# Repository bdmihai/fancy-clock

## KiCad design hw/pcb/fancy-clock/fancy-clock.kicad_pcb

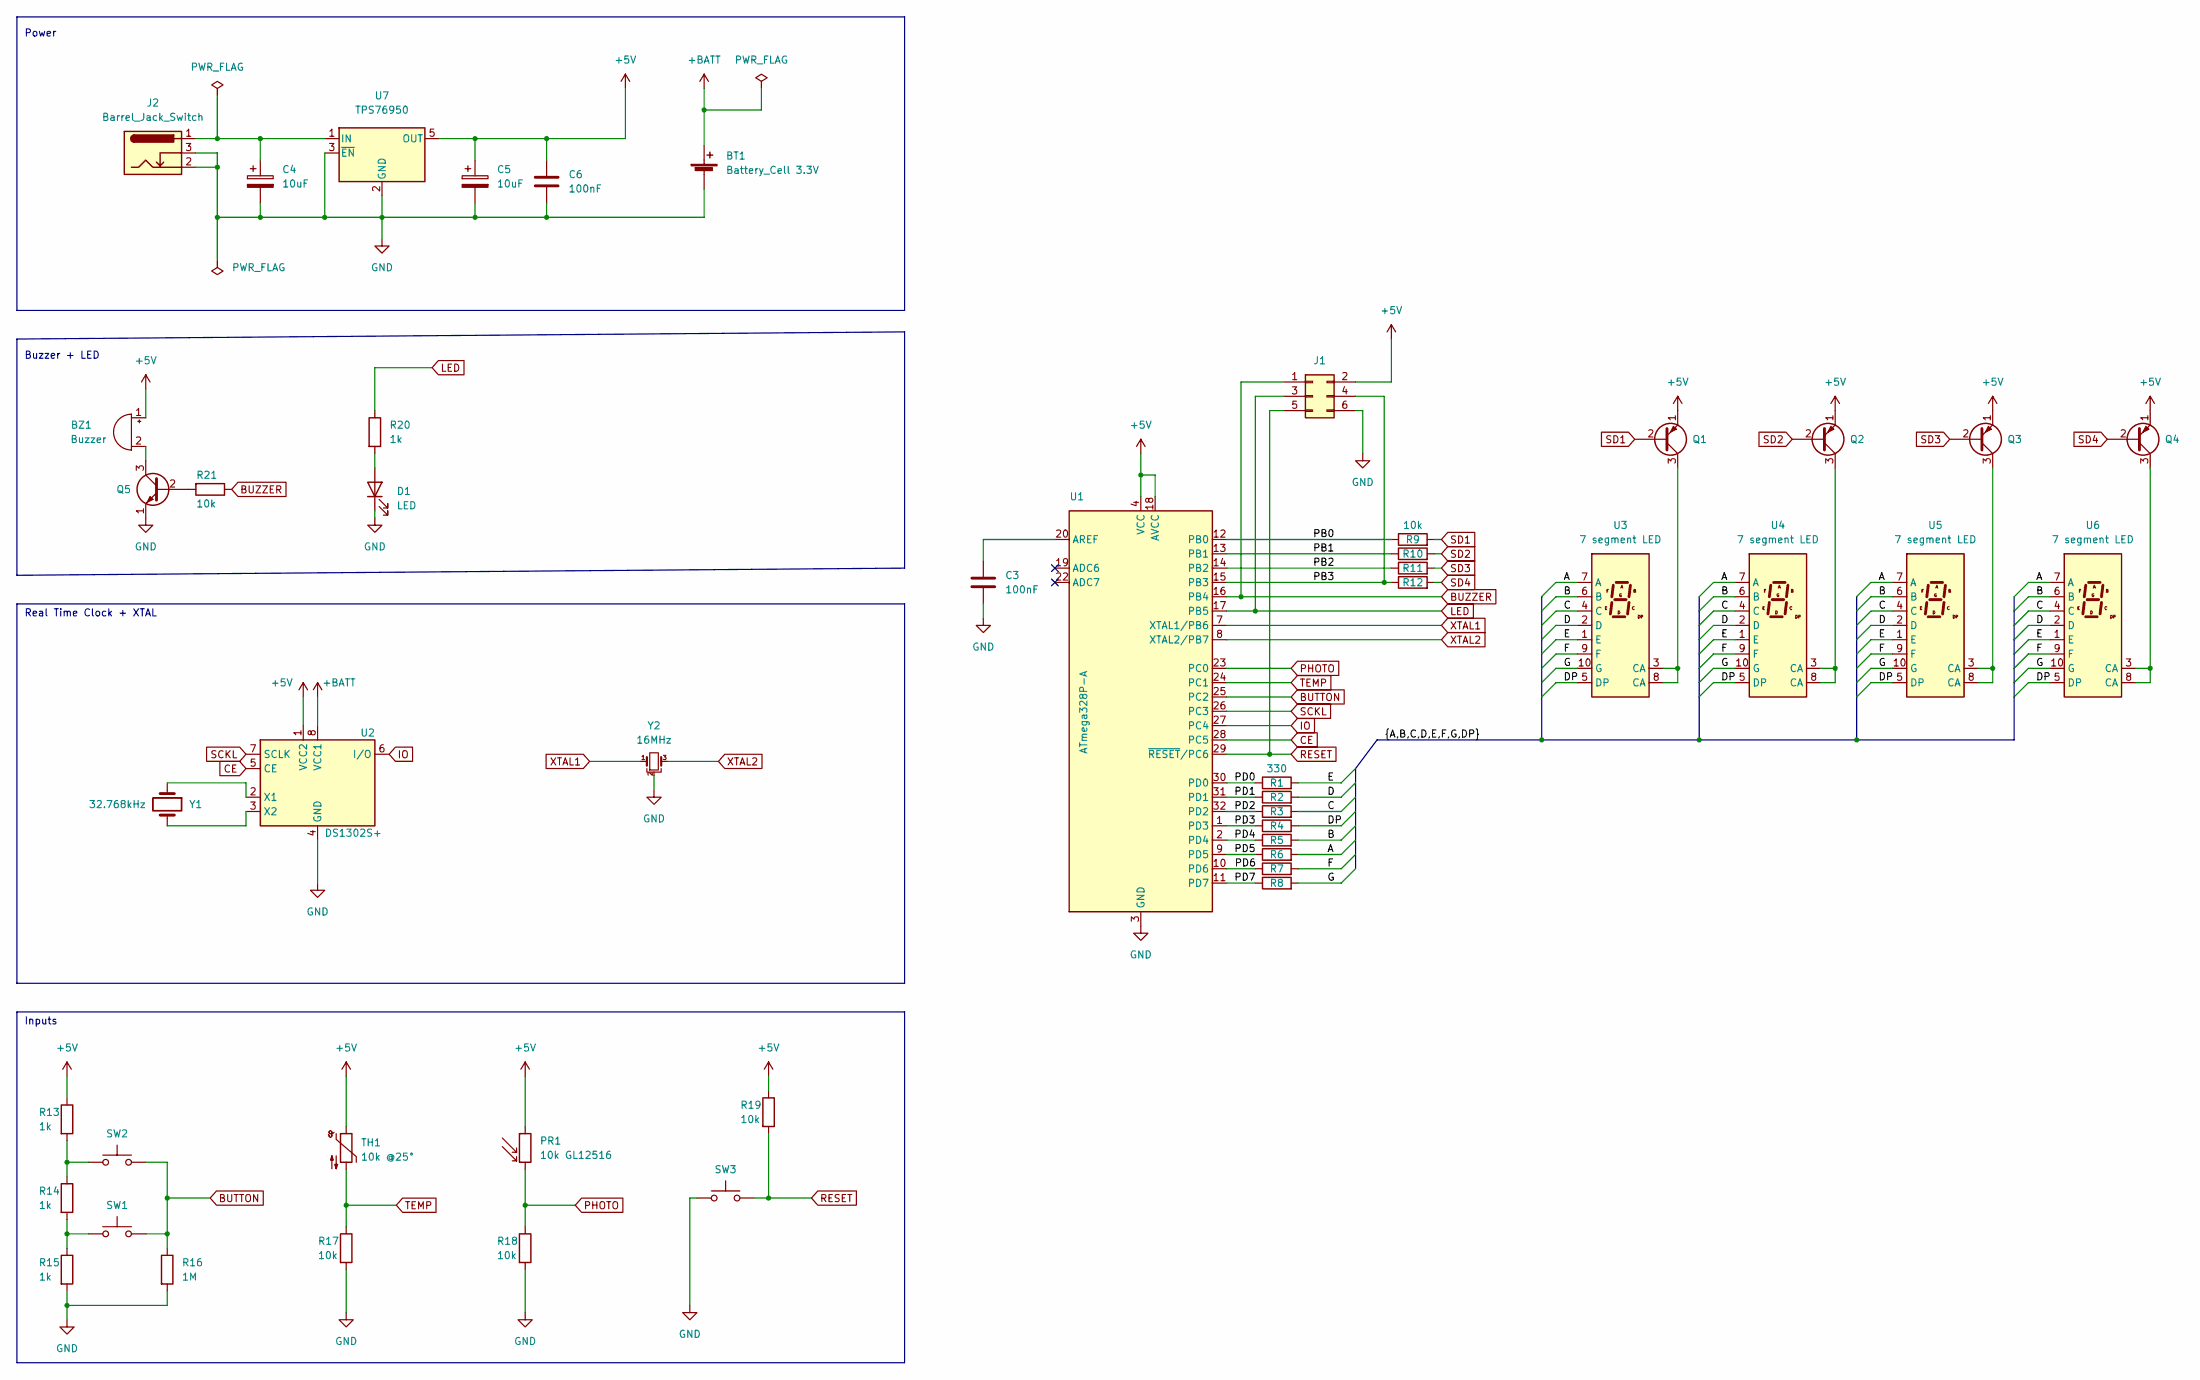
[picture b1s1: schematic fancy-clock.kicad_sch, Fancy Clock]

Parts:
BT1: Battery_Cell 3.3V; BatteryHolder_Keystone_103_1x20mm
BZ1: Buzzer; Buzzer_12x9.5RM7.6
C3, C6: 100nF; C_0805_2012Metric_Pad1.18x1.45mm_HandSolder
C4, C5: 10uF; C_1206_3216Metric_Pad1.33x1.80mm_HandSolder
D1: LED; LED_0805_2012Metric_Pad1.15x1.40mm_HandSolder
J1: Conn_02x03_Odd_Even; PinHeader_2x03_P2.54mm_Vertical
J2: Barrel_Jack_Switch; BarrelJack_Horizontal
PR1: 10k GL12516; R_Axial_DIN0204_L3.6mm_D1.6mm_P2.54mm_Vertical
Q1, Q2, Q3, Q4: Q_PNP_EBC; TO-92_Inline_Wide
Q5: Q_NPN_EBC; TO-92_Inline_Wide
R1, R2, R3, R4, R5, R6, R7, R8: 330; R_1206_3216Metric_Pad1.30x1.75mm_HandSolder
R9, R10, R11, R12, R17, R18, R19, R21: 10k; R_1206_3216Metric_Pad1.30x1.75mm_HandSolder
R13, R14, R15, R20: 1k; R_1206_3216Metric_Pad1.30x1.75mm_HandSolder
R16: 1M; R_1206_3216Metric_Pad1.30x1.75mm_HandSolder
SW1, SW2, SW3: SW_Push; SW_PUSH_6mm
TH1: 10k @25°; R_Axial_DIN0204_L3.6mm_D1.6mm_P2.54mm_Vertical
U1: ATmega328P-A; TQFP-32_7x7mm_P0.8mm
U2: DS1302S+; SO-8_5.3x6.2mm_P1.27mm
U3, U4, U5, U6: 7 segment LED; 7 Segments Display
U7: TPS76950; SOT-23-5
Y1: 32.768kHz; Crystal_C38-LF_D3.0mm_L8.0mm_Horizontal
Y2: 16MHz; Resonator_SMD_Murata_CSTxExxV-3Pin_3.0x1.1mm_HandSoldering

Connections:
+5V: BZ1.1 (-), C5.1, C6.1, J1.2, PR1.1, Q1.1 (E), Q2.1 (E), Q3.1 (E), Q4.1 (E), R13.1, R19.1, TH1.1, U1.4 (VCC), U1.6 (VCC), U1.18 (AVCC), U2.1 (VCC2), U7.5 (OUT)
+BATT: BT1.1 (+), U2.8 (VCC1)
/A: R6.2, U3.7 (A), U4.7 (A), U5.7 (A), U6.7 (A)
/B: R5.2, U3.6 (B), U4.6 (B), U5.6 (B), U6.6 (B)
/C: R3.2, U3.4 (C), U4.4 (C), U5.4 (C), U6.4 (C)
/D: R2.2, U3.2 (D), U4.2 (D), U5.2 (D), U6.2 (D)
/DP: R4.2, U3.5 (DP), U4.5 (DP), U5.5 (DP), U6.5 (DP)
/E: R1.2, U3.1 (E), U4.1 (E), U5.1 (E), U6.1 (E)
/F: R7.2, U3.9 (F), U4.9 (F), U5.9 (F), U6.9 (F)
/G: R8.2, U3.10 (G), U4.10 (G), U5.10 (G), U6.10 (G)
/PB0: R9.1, U1.12 (PB0)
/PB1: R10.1, U1.13 (PB1)
/PB2: R11.1, U1.14 (PB2)
/PB3: J1.4, R12.1, U1.15 (PB3)
/PD0: R1.1, U1.30 (PD0)
/PD1: R2.1, U1.31 (PD1)
/PD2: R3.1, U1.32 (PD2)
/PD3: R4.1, U1.1 (PD3)
/PD4: R5.1, U1.2 (PD4)
/PD5: R6.1, U1.9 (PD5)
/PD6: R7.1, U1.10 (PD6)
/PD7: R8.1, U1.11 (PD7)
BUTTON: R16.1, SW1.2, SW2.2, U1.25 (PC2)
BUZZER: J1.1, R21.1, U1.16 (PB4)
CE: U1.28 (PC5), U2.5 (CE)
GND: BT1.2 (-), C3.2, C4.2, C5.2, C6.2, D1.1 (K), J1.6, J2.2, J2.3, Q5.1 (E), R15.2, R16.2, R17.2, R18.2, SW3.1, U1.3 (GND), U1.5 (GND), U1.21 (GND), U2.4 (GND), U7.2 (GND), U7.3 (~EN), Y2.2
IO: U1.27 (PC4), U2.6 (I/O)
LED: J1.3, R20.1, U1.17 (PB5)
unnamed: BZ1.2 (+), Q5.3 (C)
unnamed: C3.1, U1.20 (AREF)
unnamed: D1.2 (A), R20.2
unnamed: Q1.3 (C), U3.3 (CA), U3.8 (CA)
unnamed: Q2.3 (C), U4.3 (CA), U4.8 (CA)
unnamed: Q3.3 (C), U5.3 (CA), U5.8 (CA)
unnamed: Q4.3 (C), U6.3 (CA), U6.8 (CA)
unnamed: Q5.2 (B), R21.2
unnamed: R13.2, R14.1, SW2.1
unnamed: R14.2, R15.1, SW1.1
unnamed: U2.2 (X1), Y1.1
unnamed: U2.3 (X2), Y1.2
unnamed: C4.1, J2.1, U7.1 (IN)
PHOTO: PR1.2, R18.1, U1.23 (PC0)
RESET: J1.5, R19.2, SW3.2, U1.29 (~RESET/PC6)
SCKL: U1.26 (PC3), U2.7 (SCLK)
SD1: Q1.2 (B), R9.2
SD2: Q2.2 (B), R10.2
SD3: Q3.2 (B), R11.2
SD4: Q4.2 (B), R12.2
TEMP: R17.1, TH1.2, U1.24 (PC1)
XTAL1: U1.7 (XTAL1/PB6), Y2.1
XTAL2: U1.8 (XTAL2/PB7), Y2.3

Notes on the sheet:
Inputs
Buzzer + LED
Real Time Clock + XTAL
Power

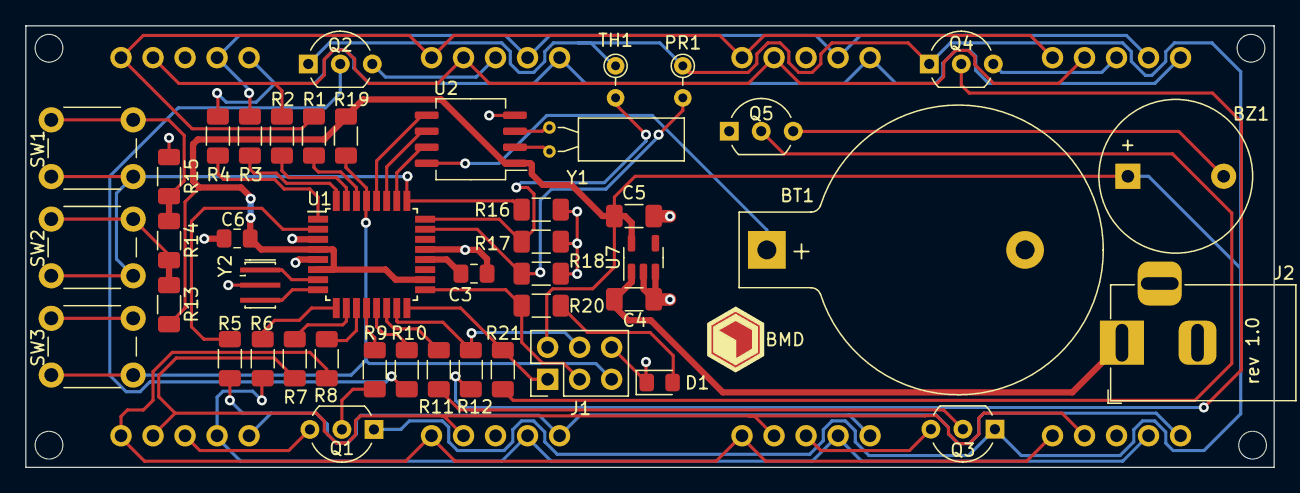
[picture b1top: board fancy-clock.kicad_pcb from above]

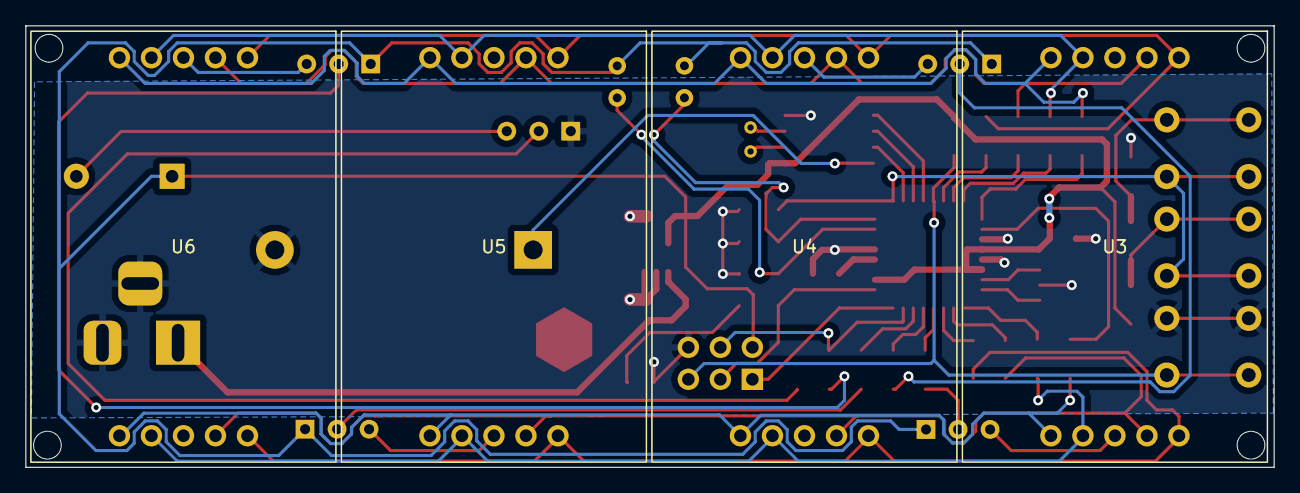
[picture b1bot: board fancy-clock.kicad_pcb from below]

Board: 2 copper layers, 99.1 x 35.0 mm, 50 parts (4 on the bottom side), 51 nets.

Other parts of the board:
BMD: logo

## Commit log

2022-04-03 initial revision
2022-04-24 fixed v1.0 errors
